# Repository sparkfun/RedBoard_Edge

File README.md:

SparkFun RedBoard Edge
========================================

[*SparkFun RedBoard Edge (DEV-14525)*](https://www.sparkfun.com/products/14525)

The RedBoard Edge is a RedBoard that's been rebuilt around the idea that projects are eventually put into an enclosure to help clean up their look.

Repository Contents
-------------------

* **/Hardware** - Eagle design files (.brd, .sch)
* **/Production** - Production panel files.

Documentation
--------------
* **[Hookup Guide](https://learn.sparkfun.com/tutorials/redboard-edge-hookup-guide)** - Basic hookup guide for the RedBoard Edge.

Product Versions
----------------
* [DEV-14525](https://www.sparkfun.com/products/14525)- SparkFun red version
* *[SPX-14471 (RETIRED)](https://www.sparkfun.com/products/retired/14471)- SparkX version*

License Information
-------------------

This product is _**open source**_! 

Please review the LICENSE.md file for license information. 

If you have any questions or concerns on licensing, please contact techsupport@sparkfun.com.

Distributed as-is; no warranty is given.

- Your friends at SparkFun.

_<COLLABORATION CREDIT>_

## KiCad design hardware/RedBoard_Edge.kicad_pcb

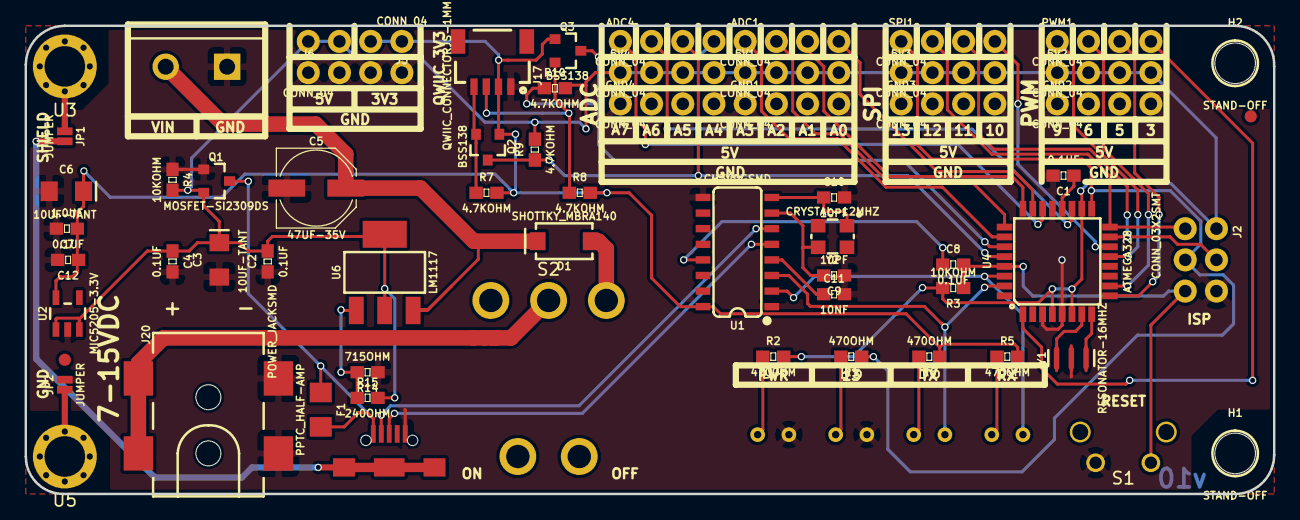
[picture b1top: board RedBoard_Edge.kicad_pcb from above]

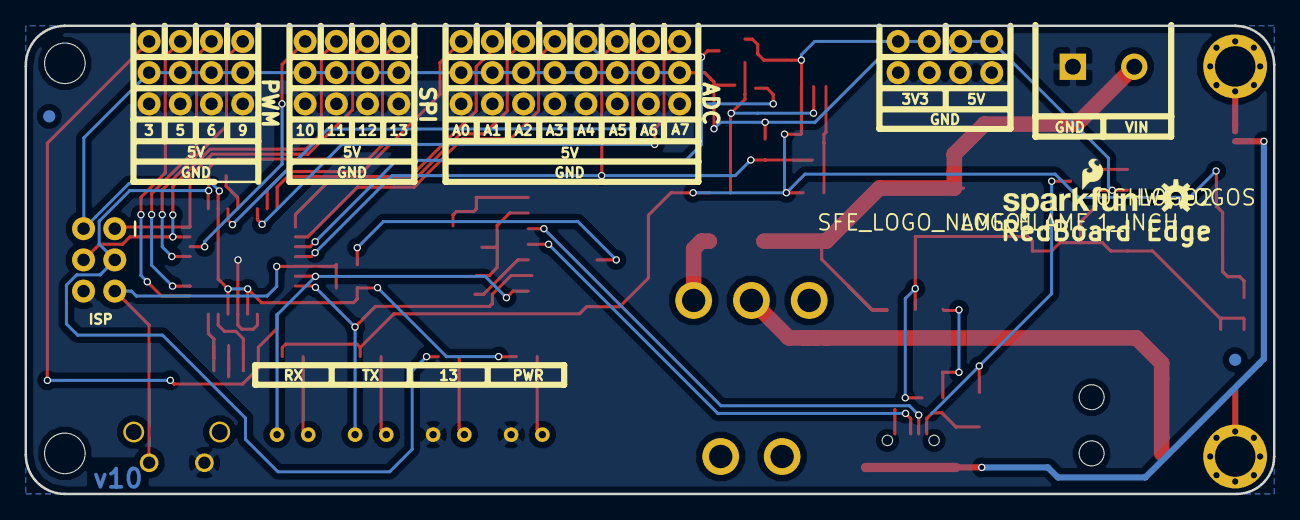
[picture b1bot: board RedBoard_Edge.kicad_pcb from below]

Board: 2 copper layers, 101.6 x 38.1 mm, 72 parts (4 on the bottom side), 46 nets.

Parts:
5V1, 5V2, 5V3, 5V4: CONN_04; 1X04_NO_SILK
ADC1, ADC4: CONN_04; 1X04_NO_SILK
C1, C2, C4, C8, C12: 0.1UF; 0603
C3, C6: 10UF-TANT; EIA3216
C5: 47UF-35V; PANASONIC_D
C7: 1.0UF; 0603
C9, C10: 10PF; 0603
C11: 10NF; 0603
D1: SHOTTKY_MBRA140; SMA-DIODE
D2: LED-YELLOW; LED_550_T1-.75_RT_ANG_PCB
D3: LED-GREEN; LED_550_T1-.75_RT_ANG_PCB
D4: LED-RED; LED_550_T1-.75_RT_ANG_PCB
D5: LED-BLUE; LED_550_T1-.75_RT_ANG_PCB
F1: PPTC_HALF-AMP; 1206
FD1, FD2, FD3, FD4: FIDUCIAL1X2; FIDUCIAL-1X2
GND1, GND2, GND3, GND4: CONN_04; 1X04_NO_SILK
H1, H2: STAND-OFF
J1: CONN_025MM; SCREWTERMINAL-5MM-2
J2: CONN_03X2SMT; 2X3-NS
J4: USB_MICRO-B; USB-B-MICRO-SMD
J5, J6: CONN_04; 1X04_NO_SILK
J17: QWIIC_CONNECTORJS-1MM; 1X04_1MM_RA
J20: POWER_JACKSMD; POWER_JACK_SMD_GND
JP1, JP2: JUMPER; SMT-JUMPER_2_NO_NO-SILK
LOGO1: SFE_LOGO_NAME_FLAME.1_INCH; SFE_LOGO_NAME_FLAME_.1
LOGO2: OSHW-LOGOS; OSHW-LOGO-S
PWM1: CONN_04; 1X04_NO_SILK
Q1: MOSFET-SI2309DS; SOT23-3
Q2, Q3: BSS138; SOT23-3
R1, R2, R5, R6: 470OHM; 0603
R3, R4: 10KOHM; 0603
R7, R8, R9, R10: 4.7KOHM; 0603
R14: 715OHM; 0603
R15: 240OHM; 0603
S1: MOMENTARY-SWITCH; SWITCH TACTILE SPST-NO 0.05A 12V
S2: SWITCH_TOGGLE; TOGGLE_SWITCH-102-C3
SPI1: CONN_04; 1X04_NO_SILK
U1: CH340GSMD; SO16
U2: MIC5205-3.3V; SOT23-5
U3, U5: Standoff_Grounding; STANDOFF_GROUNDING
U4: ATMEGA328; TQFP32-08
U6: LM1117; SOT223
Y1: RESONATOR-16MHZ; RESONATOR-SMD-3.2X1.3
Y2: CRYSTAL-12MHZ; CRYSTAL-SMD-3.2X2.5MM

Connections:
3.3V: C6.+, C7.1, C12.1, J5.1, J5.2, J17.2, Q2.1, Q3.1, R5.2, R6.1, R7.2, R8.2, U1.16, U2.5
5V: 5V1.1, 5V1.2, 5V1.3, 5V1.4, 5V2.1, 5V2.2, 5V2.3, 5V2.4, 5V3.1, 5V3.2, 5V3.3, 5V3.4, 5V4.1, 5V4.2, 5V4.3, 5V4.4, C2.2, C3.+, C4.1, J2.2, J5.3, J5.4, Q1.2, R2.2, R3.2, R4.2, R9.2, R10.2, R15.2, U2.1, U2.3, U4.4, U4.6, U4.18, U6.2, U6.4
/AD0: ADC1.4, U4.23
/AD1: ADC1.3, U4.24
/AD2: ADC1.2, U4.25
/AD3: ADC1.1, U4.26
/AD6: ADC4.2, U4.19
/AD7: ADC4.1, U4.22
/AREF: C1.1, U4.20
/DTR: C8.1, U1.13
/HI_SCL: ADC4.3, Q2.3, R9.1, U4.28
/HI_SDA: ADC4.4, Q3.3, R10.1, U4.27
/MISO: J2.1, SPI1.2, U4.16
/MOSI: J2.4, SPI1.3, U4.15
/PWM3: PWM1.4, U4.1
/PWM5: PWM1.3, U4.9
/PWM6: PWM1.2, U4.10
/PWM9: PWM1.1, U4.13
/RESET: C8.2, J2.5, R3.1, S1.2, U4.29
/RXI: D2.1, U1.2, U4.30
/SCK: J2.3, R1.1, SPI1.1, U4.17
/SCL: J17.4, Q2.2, R7.1
/SDA: J17.3, Q3.2, R8.1
/SS: SPI1.4, U4.14
/TXO: D3.1, U1.3, U4.31
/USBVCC: F1.1, Q1.3
/usb_shield: J4.SHIE, JP1.2
GND: C1.2, C2.1, C3.-, C4.2, C5.-, C6.-, C7.2, C9.1, C10.2, C11.2, C12.2, D4.1, D5.1, GND1.1, GND1.2, GND1.3, GND1.4, GND2.1, GND2.2, GND2.3, GND2.4, GND3.1, GND3.2, GND3.3, GND3.4, GND4.1, GND4.2, GND4.3, GND4.4, J1.1, J2.6, J4.GND, J6.1, J6.2, J6.3, J6.4, J17.1, J20.GND, JP2.2, Q1.1, R4.1, R14.1, S1.1, U1.1, U1.9, U2.2, U4.3, U4.5, U4.21, Y1.2
unnamed: C9.2, U1.7, Y2.3
unnamed: C10.1, U1.8, Y2.1
unnamed: C11.1, U1.4
unnamed: D1.A, S2.3
unnamed: D2.2, R5.1
unnamed: D3.2, R6.2
unnamed: D4.2, R2.1
unnamed: D5.2, R1.2
unnamed: F1.2, J4.VBUS
unnamed: J4.D+, U1.5
unnamed: J4.D-, U1.6
unnamed: J20.VIN0, S2.2
unnamed: JP1.1, U3.1
unnamed: JP2.1, U5.1
unnamed: R14.2, R15.1, U6.1
unnamed: U4.7, Y1.1
unnamed: U4.8, Y1.3
VIN: C5.+, D1.C, J1.2, U6.3

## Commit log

2017-10-26 conversion to Reds, all parts now point to KiCad library in directory C:/Github
2017-11-02 Conversion to Reds
2017-11-03 Post Design review changes
2017-11-03 Checklist changes
2017-11-03 forgot to save before commit
2017-11-07 QC Double Check Issues
2017-11-09 Post double double check changes
2017-11-14 fixed gerbers
2017-12-18 updated 12mhz crystal
2018-01-02 cleaned repo
2018-01-03 post design review changes, added switch
2018-01-04 added CC 4.0
2018-01-05 Post double check changes
2018-01-19 updated toggle switch
2018-02-02 fixed xtal
2018-02-07 removed circle
2018-02-08 Fixed broken kicad file
2018-02-09 QC Checklist changes
2018-02-13 panel
2018-05-31 cleaning repo
2018-05-31 fixed typo
2018-06-01 attampting to remove extra hardware files
2018-06-01 fixing repo

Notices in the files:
hardware/RedBoard_Edge.kicad_pcb:
Released under the Creative Commons Attribution Share-Alike 4.0 License
